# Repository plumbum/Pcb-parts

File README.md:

Circuit parts
=============

This project contains typical schematic and PCB parts
in Eagle CAD format.

(CC) 2009-2011 ivan@tuxotronic.org

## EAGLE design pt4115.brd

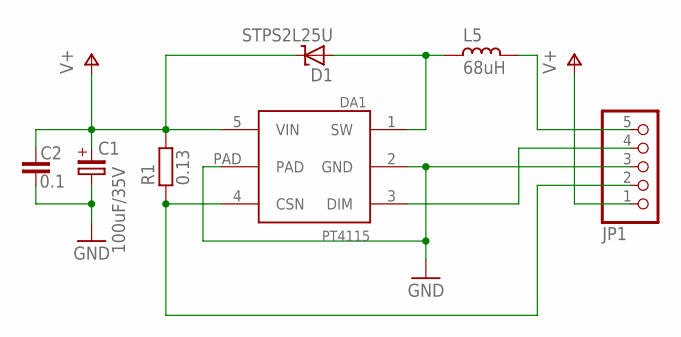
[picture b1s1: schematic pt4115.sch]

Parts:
C1: 100uF/35V; CE-025X060
C2: 0.1; C0805
D1: STPS2L25U; SMB_1
DA1: PT4115; SOT89-5
JP1: PINHD-1X5_2.54-90°; 1X05/90
L5: 68uH; CD54
R1: 0.13; R1206

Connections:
GND: C1.-, C2.2, DA1.2 (GND), DA1.PAD, JP1.3
unnamed: DA1.4 (CSN), JP1.2, R1.1
unnamed: JP1.5, L5.1
unnamed: DA1.3 (DIM), JP1.4
SW4: D1.A, DA1.1 (SW), L5.2
V+: C1.+, C2.1, D1.C, DA1.5 (VIN), JP1.1, R1.2

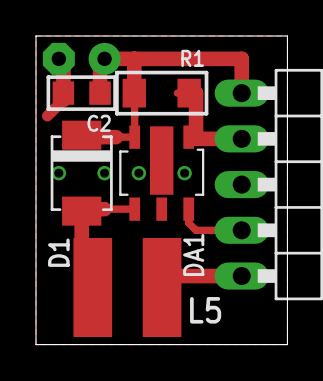
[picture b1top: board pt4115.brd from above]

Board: 2 copper layers, 14.0 x 17.1 mm, 7 parts (1 on the bottom side), 6 nets.

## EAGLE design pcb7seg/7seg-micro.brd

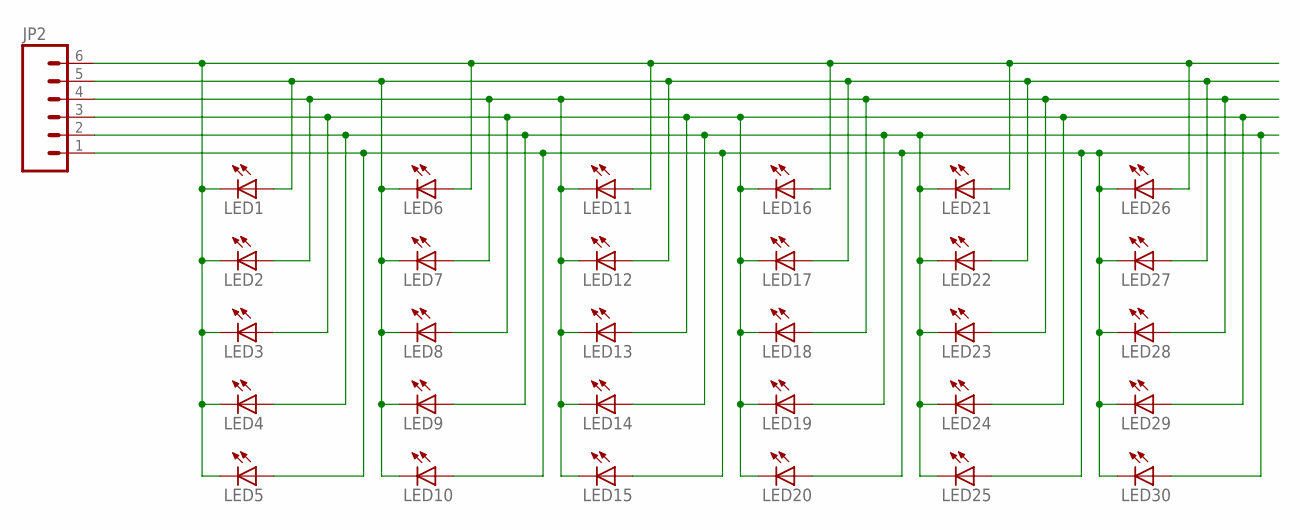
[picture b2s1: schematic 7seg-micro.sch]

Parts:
JP2: M06NO_SILK_FEMALE_PTH; 1X06_NO_SILK
LED1, LED2, LED3, LED4, LED5, LED6, LED7, LED8, LED9, LED10, LED11, LED12, LED13, LED14, LED15, LED16, LED17, LED18, LED19, LED20, LED21, LED22, LED23, LED24, LED25, LED26, LED27, LED28, LED29, LED30: LED0603; LED-0603

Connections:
COL1: JP2.6, LED1.C, LED2.C, LED3.C, LED4.C, LED5.C, LED6.A, LED11.A, LED16.A, LED21.A, LED26.A
COL2: JP2.5, LED1.A, LED6.C, LED7.C, LED8.C, LED9.C, LED10.C, LED12.A, LED17.A, LED22.A, LED27.A
COL3: JP2.4, LED2.A, LED7.A, LED11.C, LED12.C, LED13.C, LED14.C, LED15.C, LED18.A, LED23.A, LED28.A
COL4: JP2.3, LED3.A, LED8.A, LED13.A, LED16.C, LED17.C, LED18.C, LED19.C, LED20.C, LED24.A, LED29.A
COL5: JP2.2, LED4.A, LED9.A, LED14.A, LED19.A, LED21.C, LED22.C, LED23.C, LED24.C, LED25.C, LED30.A
COL6: JP2.1, LED5.A, LED10.A, LED15.A, LED20.A, LED25.A, LED26.C, LED27.C, LED28.C, LED29.C, LED30.C

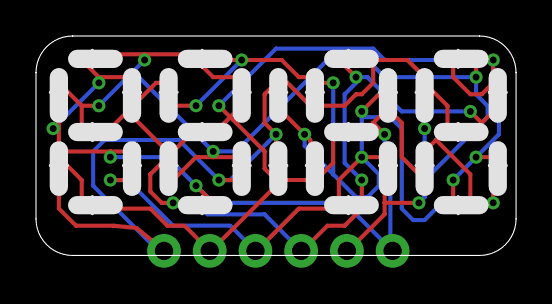
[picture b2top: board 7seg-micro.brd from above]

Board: 2 copper layers, 26.7 x 12.2 mm, 31 parts (0 on the bottom side), 6 nets.

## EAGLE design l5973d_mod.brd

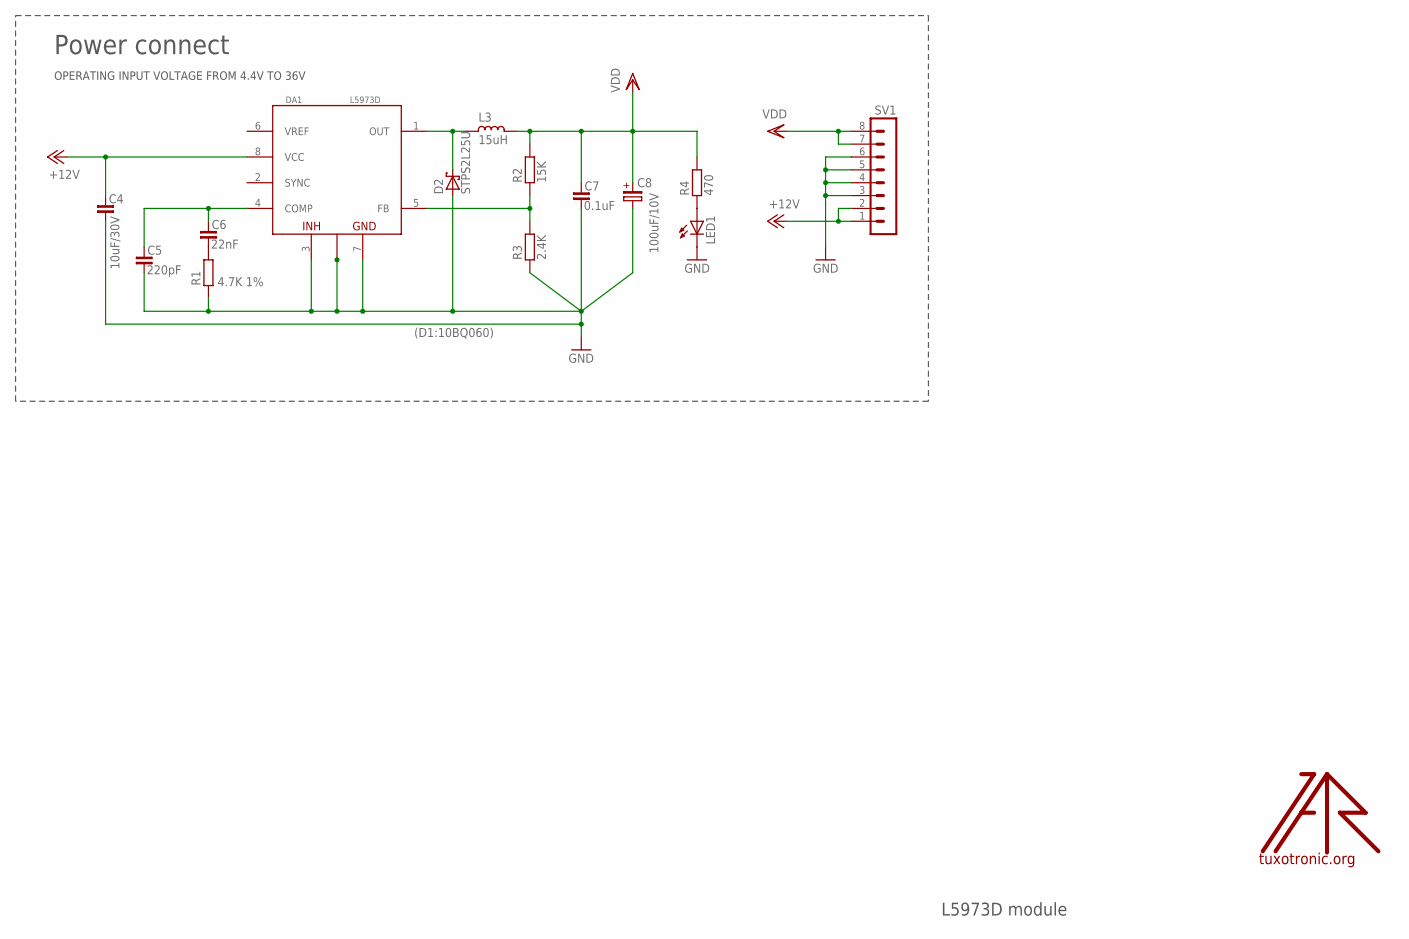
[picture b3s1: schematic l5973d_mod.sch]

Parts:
C4: 10uF/30V; C1210
C5: 220pF; C0603
C6: 22nF; C0603
C7: 0.1uF; C0805
C8: 100uF/10V; CE-035X080
D2: STPS2L25U; SMB
DA1: L5973D; HSOP8-PAD
L3: 15uH; CD75
LED1: LEDCHIPLED_0805; CHIPLED_0805
R1: 4.7K 1%; R0603
R2: 15K; R0603
R3: 2.4K; R0603
R4: 470; R0603
SV1: MA08-1W
U$1: LOGO; TT_LOGO

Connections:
+12V: C4.1, DA1.8 (VCC), SV1.1, SV1.2
GND: C4.2, C5.2, C7.2, C8.-, D2.A, DA1.3 (INH), DA1.7 (GND), DA1.P (GND), LED1.C, R1.1, R3.1, SV1.3, SV1.4, SV1.5, SV1.6
unnamed: LED1.A, R4.1
unnamed: D2.C, DA1.1 (OUT), L3.2
unnamed: DA1.5 (FB), R2.1, R3.2
unnamed: C6.2, R1.2
unnamed: C5.1, C6.1, DA1.4 (COMP)
VDD: C7.1, C8.+, L3.1, R2.2, R4.2, SV1.7, SV1.8

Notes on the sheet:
L5973D module
Power connect
(D1:10BQ060)
OPERATING INPUT VOLTAGE FROM 4.4V TO 36V

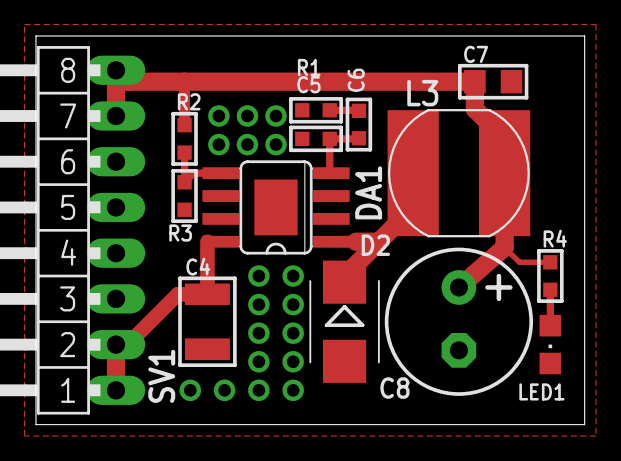
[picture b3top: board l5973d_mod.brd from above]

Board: 2 copper layers, 30.5 x 21.6 mm, 15 parts (1 on the bottom side), 8 nets.

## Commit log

2011-02-27 Init
2011-02-27 max232 pcb fixes
2011-03-18 nokia 1202 lcd print
2011-04-04 lcd nokia 1202
2011-04-04 led driver
2011-04-04 attiny2313 usb 1.0
2011-04-05 mbi6651 fix package
2011-04-07 GTL2003 level translator example
2011-07-03 7805 replace
2011-07-05 din box
2011-07-08 Gainta DIN boxes
2011-08-02 Gainta box D4MG lcd panel started
2011-08-11 lcd1616 power
2011-08-11 interface pcb done
2011-08-12 box-din4-lcd production
2011-10-12 waterproof boxes
2011-11-14 mc34063 step-up boost converter
2012-10-24 vl100 discovery dock
2012-12-23 tda2003 board
2013-05-06 power amp pcb
2013-05-16 Propeller plug board
2013-05-16 l6219 devboard
2013-05-17 L6219DS simple for lut
2013-05-19 L6219 lut pcb done
2013-06-03 L5973 2A dc-dc module
2014-09-04 kinder surprize box
2015-10-22 PT4115 LED driver demo module (unchecked)
2017-09-22 fix PT4115 led driver
2017-09-22 esp8622 library
2017-09-22 DIN3 box fixes
2018-01-06 7seg pcb sample
2018-01-06 pt4115 fix to cd43 inductor
2018-01-06 pt4115 sch png
2018-01-06 pt4115 fixes

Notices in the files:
parts and their libraries:
SparkFun-Connectors: Licensing: Creative Commons ShareAlike 4.0 International - https://creativecommons.org/licenses/by-sa/4.0
rc-master-smd: Copyright (C) 2007, Bob Starr
